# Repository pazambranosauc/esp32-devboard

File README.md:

# ESP32 Development Board (KiCad)

A two-layer ESP32-WROOM-32 development board designed from a blank schematic: USB-C, an AMS1117-3.3 regulator, a CP2102N USB-UART bridge with two-transistor auto-reset, and two breadboard-spaced 20-pin headers. It's sized for hand assembly: 0603 passives, 1206 tantalums, 2.54 mm headers.

**Status: Rev B layout complete, not yet fabricated.** Rev A was cancelled before production after a design review found three faults (below). Bring-up results will be added here once the boards arrive.

| Top | Bottom |
|---|---|
|  |  |

## Specs

| | |
|---|---|
| Board | 30.0 × 64.0 mm, 2 layers, GND pour on both layers |
| MCU | ESP32-WROOM-32 (antenna keep-out on every layer, no copper under the antenna) |
| USB | USB-C receptacle (GCT USB4105), USB 2.0, 5.1 kΩ on CC1 and CC2 so it works either way up |
| USB-UART | CP2102N (QFN-24), DTR/RTS auto-reset through two MMBT3904s |
| Power | 5 V USB → AMS1117-3.3, 10 µF tantalum in and out, 100 nF decoupling at each IC |
| I/O | 2 × 20-pin 2.54 mm headers, rows 25.4 mm apart (fits a breadboard) |
| Buttons | EN (reset) and IO0 (boot) |
| Routing | 0.25 mm signals, 0.5 mm power (USB_VBUS, VDD, GND), necked down to 0.2 mm at fine-pitch pins |

## How it works

```
USB-C ─┬─ VBUS ──┬─ AMS1117-3.3 ── VDD (3.3 V) ─┬─ ESP32-WROOM-32
       │         └─ CP2102N VREGIN / VBUS        └─ CP2102N VIO, pull-ups, headers
       ├─ D+/D− ─── CP2102N ── TXD/RXD ───────────── ESP32 RXD0/TXD0
       │                    └─ DTR/RTS ─ Q1/Q2 ──── EN / IO0   (auto-reset into bootloader)
       └─ CC1/CC2 ─ 5.1 kΩ each to GND (identifies the board as a USB sink)
```

## Rev A → Rev B: what broke and what I changed

Rev A was laid out and submitted to JLCPCB. A net-by-net review of the board file found three faults, so I cancelled the order before it went into production.

| # | Rev A fault | Why it was missed | Rev B fix |
|---|---|---|---|
| 1 | **The 3.3 V regulator had no input.** USB 5 V (`USB_VBUS`) only reached the CP2102N's VREGIN pin. The AMS1117's input was on a separate net (`UART_VBUS`) tied only to the CP2102N's VBUS *sense* pin. The input caps were in series instead of to GND. The board would never have powered on. | A `PWR_FLAG` on the regulator input told ERC the net was powered, which hid the error. | USB 5 V feeds the regulator and both CP2102N VBUS pins, the caps go to GND, and the masking `PWR_FLAG` is removed. |
| 2 | **The reset and boot buttons did nothing.** Each switch pulled EN or IO0 to GND through a reverse-biased LED, so the pin never went low. | ERC can't see it: every connection is valid, only the diode direction is wrong. | The switches go directly to EN and IO0, and the LEDs are removed. |
| 3 | **Auto-reset was AC-coupled.** The transistor bases were driven through 100 nF capacitors instead of resistors, giving only edge pulses where esptool needs IO0 held low while EN rises. | ERC can't see it: the topology is right, only the component type is wrong. | 10 kΩ base resistors (R10, R11). |

Also changed for Rev B:
- **USB-C plug → receptacle,** so it works with a normal cable. CC1 and CC2 each have their own 5.1 kΩ, and both D+/D− contact pairs are tied.
- **1.00 mm → 2.54 mm headers.** The 1 mm headers had 0.15 mm between pads, far below JLCPCB's 0.5 mm minimum for through-holes, and wouldn't fit a breadboard.
- **0201 resistors and 1808 caps → 0603, and 10 µF electrolytics → 1206 tantalums,** for hand soldering.
- **ESP32 ground-pad vias 0.2 → 0.3 mm,** JLCPCB's 2-layer minimum.
- **EN RC 10 kΩ / 1 µF,** as Espressif recommends.
- **GND pour on both layers,** replacing a front-only pour that had broken into islands.

The original Rev A schematic is kept in [`hardware/rev-a/`](hardware/rev-a), with a [screenshot](docs/images/schematic-rev-a.png), for comparison.

| Layout, front copper | Layout, back copper |
|---|---|
|  |  |

## Verification so far

- **ERC:** re-run on the final schematic before fabrication.
- **DRC:** 0 errors, 0 unconnected items. Accepted violations, each documented:
  - **4 × hole clearance:** the USB4105's GND pads sit 0.19 mm from its own plastic locating-peg holes in the manufacturer footprint. JLCPCB trims copper around non-plated holes.
  - **1 × library mismatch on U2:** from the deliberate via-drill change.
- **Independent net check:** a script compared every pad on the board against the schematic netlist (62 nets, 0 mismatches) and confirmed every net is fully connected in copper.
- **Not yet verified:** fabrication, assembly and power-up. Planned bring-up:
  1. Check 3.3 V with no ESP32 fitted.
  2. Check the CP2102N enumerates.
  3. Scope EN and IO0 during an auto-reset.
  4. Flash a blink sketch.

## Bill of materials

| Ref | Value | Footprint | Qty |
|---|---|---|---|
| U2 | ESP32-WROOM-32 | `RF_Module:ESP32-WROOM-32` | 1 |
| U3 | CP2102N (e.g. CP2102N-A02-GQFN24) | `QFN-24-1EP_4x4mm_P0.5mm_EP2.6x2.6mm` | 1 |
| U1 | AMS1117-3.3 | `SOT-223-3_TabPin2` | 1 |
| P1 | USB-C receptacle, 16-pin (GCT USB4105-GF-A) | `USB_C_Receptacle_GCT_USB4105-xx-A_16P_TopMnt_Horizontal` | 1 |
| Q1, Q2 | MMBT3904 | `SOT-23` | 2 |
| C1, C3, C9 | 10 µF tantalum (C1 ≥ 16 V, C3/C9 ≥ 10 V) | `CP_EIA-3216-18_Kemet-A_HandSolder` | 3 |
| C2, C4, C8 | 100 nF | `C_0603_1608Metric` | 3 |
| C5 | 1 µF | `C_0603_1608Metric` | 1 |
| R1, R5, R7, R8, R10, R11 | 10 kΩ | `R_0603_1608Metric` | 6 |
| R2, R3 | 5.1 kΩ | `R_0603_1608Metric` | 2 |
| R6 | 1 MΩ | `R_0603_1608Metric` | 1 |
| SW1, SW2 | Tactile switch (Alps SKRK) | `SW_Push_SPST_NO_Alps_SKRK` | 2 |
| J1, J2 | 1×20 male header, 2.54 mm | `PinHeader_1x20_P2.54mm_Vertical` | 2 |

## Open the project

KiCad 9. Open `hardware/Customized ESP-32.kicad_pro`; open the schematic and board through the project so they stay linked.

```
hardware/
  Customized ESP-32.kicad_pro   project
  Customized ESP-32.kicad_sch   schematic (rev B)
  Customized ESP-32.kicad_pcb   board (rev B)
  Customized ESP-32.kicad_dru   custom design rules
  rev-a/                        original rev A schematic, kept for comparison
docs/images/                    renders, layout and schematic screenshots
```

---
Pedro Zambrano-Saucedo · Electrical Engineering, UTEP · [Portfolio](https://pazambranosauc.github.io/pazambranosauc/)

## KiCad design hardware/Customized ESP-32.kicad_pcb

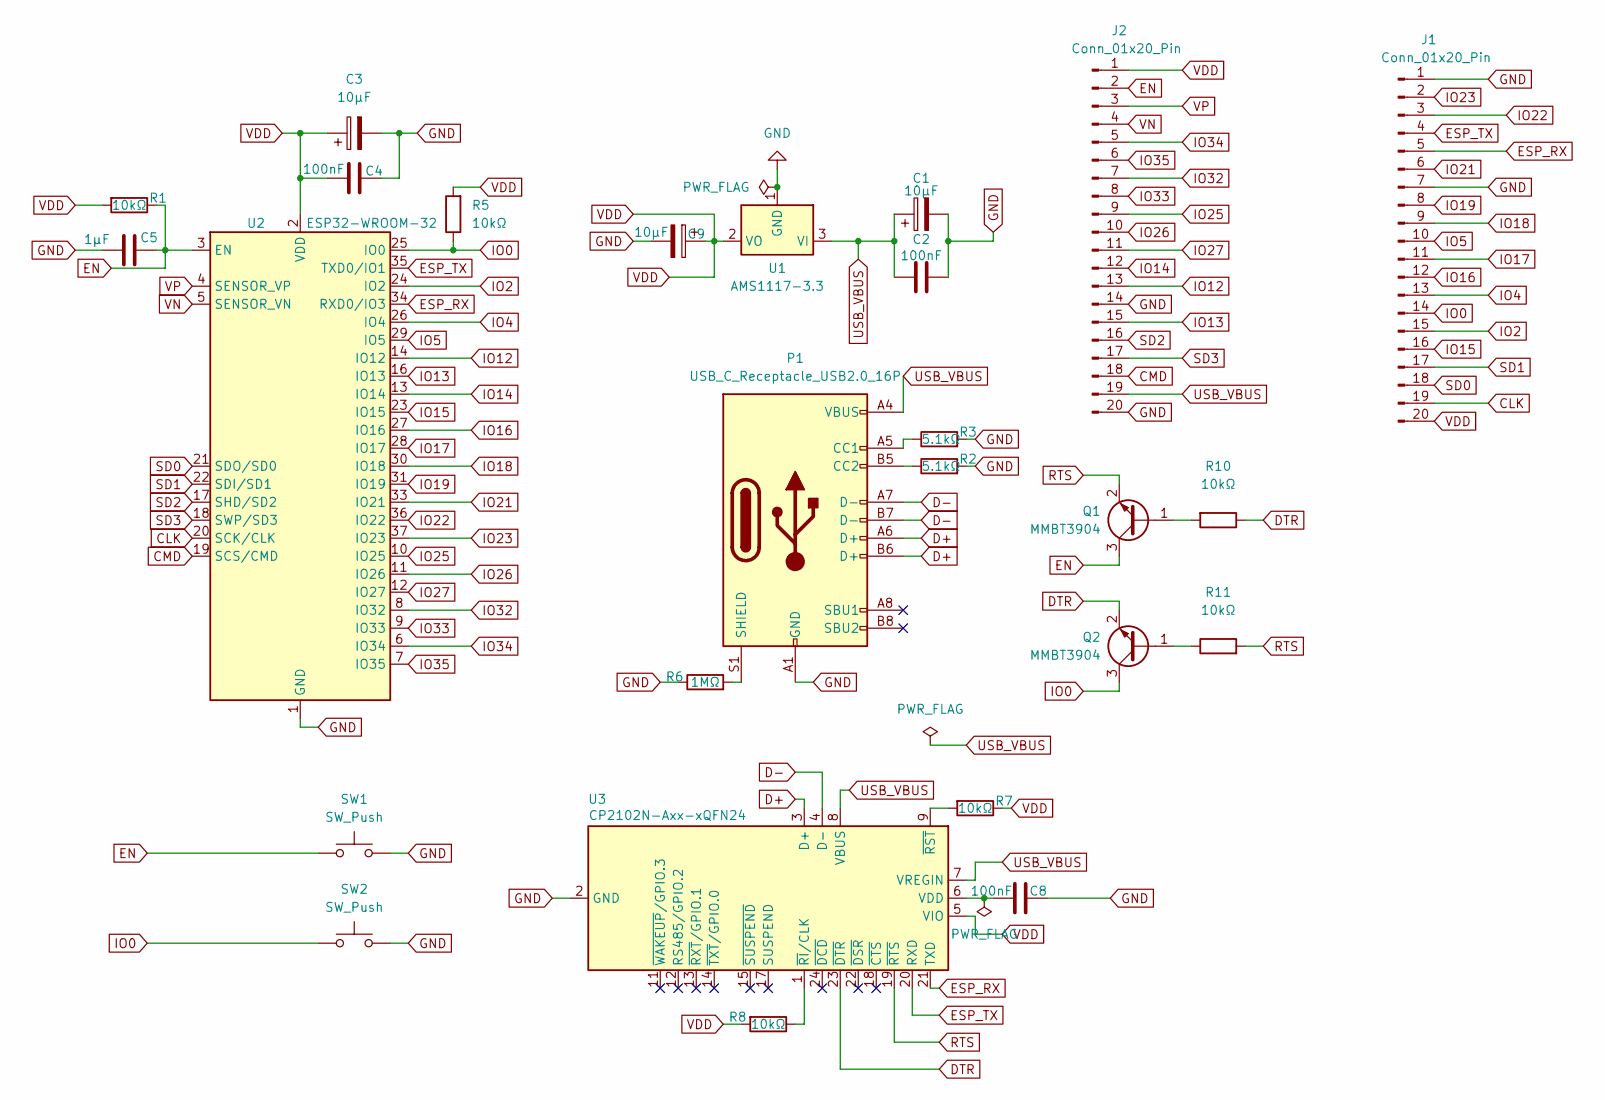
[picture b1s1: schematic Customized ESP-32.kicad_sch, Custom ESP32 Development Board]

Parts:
C1, C9: 10μF; CP_EIA-3216-18_Kemet-A_HandSolder
C2, C4, C8: 100nF; C_0603_1608Metric_Pad1.08x0.95mm_HandSolder
C3: 10µF; CP_EIA-3216-18_Kemet-A_HandSolder
C5: 1µF; C_0603_1608Metric_Pad1.08x0.95mm_HandSolder
J1, J2: Conn_01x20_Pin; PinHeader_1x20_P2.54mm_Vertical
P1: USB_C_Receptacle_USB2.0_16P; USB_C_Receptacle_GCT_USB4105-xx-A_16P_TopMnt_Horizontal
Q1, Q2: MMBT3904; SOT-23
R1, R5, R7, R8, R10, R11: 10kΩ; R_0603_1608Metric_Pad0.98x0.95mm_HandSolder
R2, R3: 5.1kΩ; R_0603_1608Metric_Pad0.98x0.95mm_HandSolder
R6: 1MΩ; R_0603_1608Metric_Pad0.98x0.95mm_HandSolder
SW1, SW2: SW_Push; SW_Push_SPST_NO_Alps_SKRK
U1: AMS1117-3.3; SOT-223-3_TabPin2
U2: ESP32-WROOM-32
U3: CP2102N-Axx-xQFN24; QFN-24-1EP_4x4mm_P0.5mm_EP2.6x2.6mm

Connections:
CLK: J1.19, U2.20 (SCK/CLK)
CMD: J2.18, U2.19 (SCS/CMD)
D+: P1.A6 (D+), P1.B6 (D+), U3.3 (D+)
D-: P1.A7 (D-), P1.B7 (D-), U3.4 (D-)
DTR: Q2.2 (E), R10.1, U3.23 (~DTR)
EN: C5.2, J2.2, Q1.3 (C), R1.1, SW1.1, U2.3 (EN)
ESP_RX: J1.5, U2.34 (RXD0/IO3), U3.21 (TXD)
ESP_TX: J1.4, U2.35 (TXD0/IO1), U3.20 (RXD)
GND: C1.2, C2.2, C3.2, C4.2, C5.1, C8.1, C9.2, J1.1, J1.7, J2.14, J2.20, P1.A1 (GND), P1.A12 (GND), P1.B1 (GND), P1.B12 (GND), R2.2, R3.2, R6.1, SW1.2, SW2.2, U1.1 (GND), U2.1 (GND), U2.15 (GND), U2.38 (GND), U2.39 (GND), U3.2 (GND), U3.25 (GND)
IO0: J1.14, Q2.3 (C), R5.1, SW2.1, U2.25 (IO0)
IO2: J1.15, U2.24 (IO2)
IO4: J1.13, U2.26 (IO4)
IO5: J1.10, U2.29 (IO5)
IO12: J2.13, U2.14 (IO12)
IO13: J2.15, U2.16 (IO13)
IO14: J2.12, U2.13 (IO14)
IO15: J1.16, U2.23 (IO15)
IO16: J1.12, U2.27 (IO16)
IO17: J1.11, U2.28 (IO17)
IO18: J1.9, U2.30 (IO18)
IO19: J1.8, U2.31 (IO19)
IO21: J1.6, U2.33 (IO21)
IO22: J1.3, U2.36 (IO22)
IO23: J1.2, U2.37 (IO23)
IO25: J2.9, U2.10 (IO25)
IO26: J2.10, U2.11 (IO26)
IO27: J2.11, U2.12 (IO27)
IO32: J2.7, U2.8 (IO32)
IO33: J2.8, U2.9 (IO33)
IO34: J2.5, U2.6 (IO34)
IO35: J2.6, U2.7 (IO35)
unnamed: P1.A5 (CC1), R3.1
unnamed: P1.B5 (CC2), R2.1
unnamed: P1.S1 (SHIELD), R6.2
unnamed: Q1.1 (B), R10.2
unnamed: Q2.1 (B), R11.1
unnamed: C8.2, U3.6 (VDD)
unnamed: R8.1, U3.1 (~RI/CLK)
unnamed: R7.2, U3.9 (~RST)
RTS: Q1.2 (E), R11.2, U3.19 (~RTS)
SD0: J1.18, U2.21 (SDO/SD0)
SD1: J1.17, U2.22 (SDI/SD1)
SD2: J2.16, U2.17 (SHD/SD2)
SD3: J2.17, U2.18 (SWP/SD3)
USB_VBUS: C1.1, C2.1, J2.19, P1.A4 (VBUS), P1.A9 (VBUS), P1.B4 (VBUS), P1.B9 (VBUS), U1.3 (VI), U3.7 (VREGIN), U3.8 (VBUS)
VDD: C3.1, C4.1, C9.1, J1.20, J2.1, R1.2, R5.2, R7.1, R8.2, U1.2 (VO), U2.2 (VDD), U3.5 (VIO)
VN: J2.4, U2.5 (SENSOR_VN)
VP: J2.3, U2.4 (SENSOR_VP)

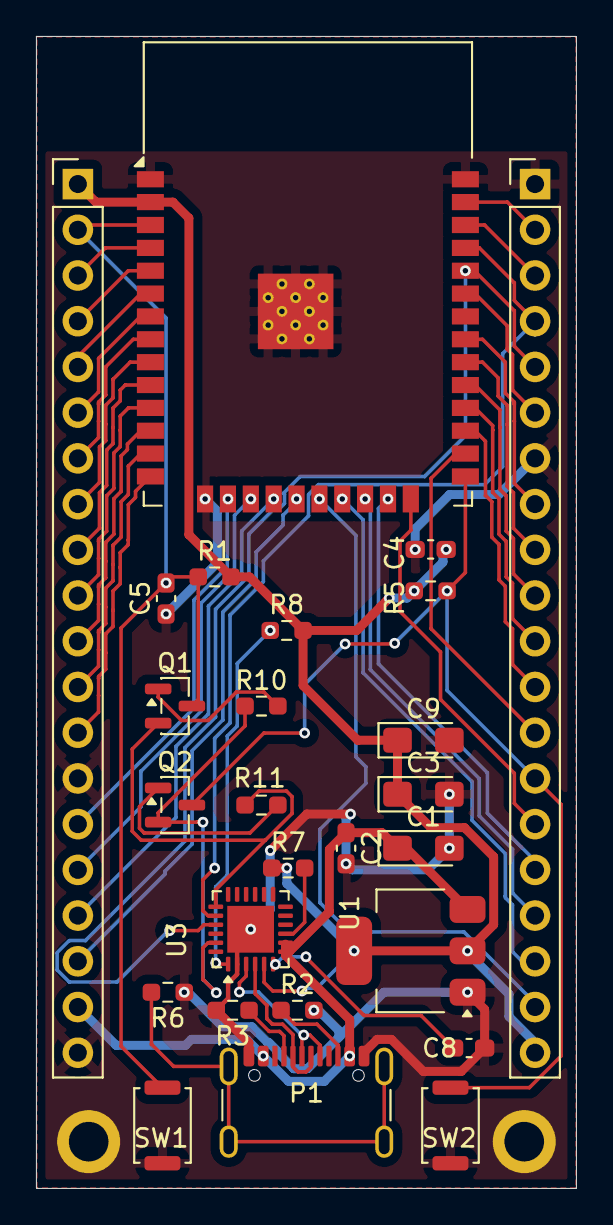
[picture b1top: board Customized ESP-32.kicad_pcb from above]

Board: 2 copper layers, 30.0 x 64.0 mm, 26 parts (0 on the bottom side), 48 nets.
